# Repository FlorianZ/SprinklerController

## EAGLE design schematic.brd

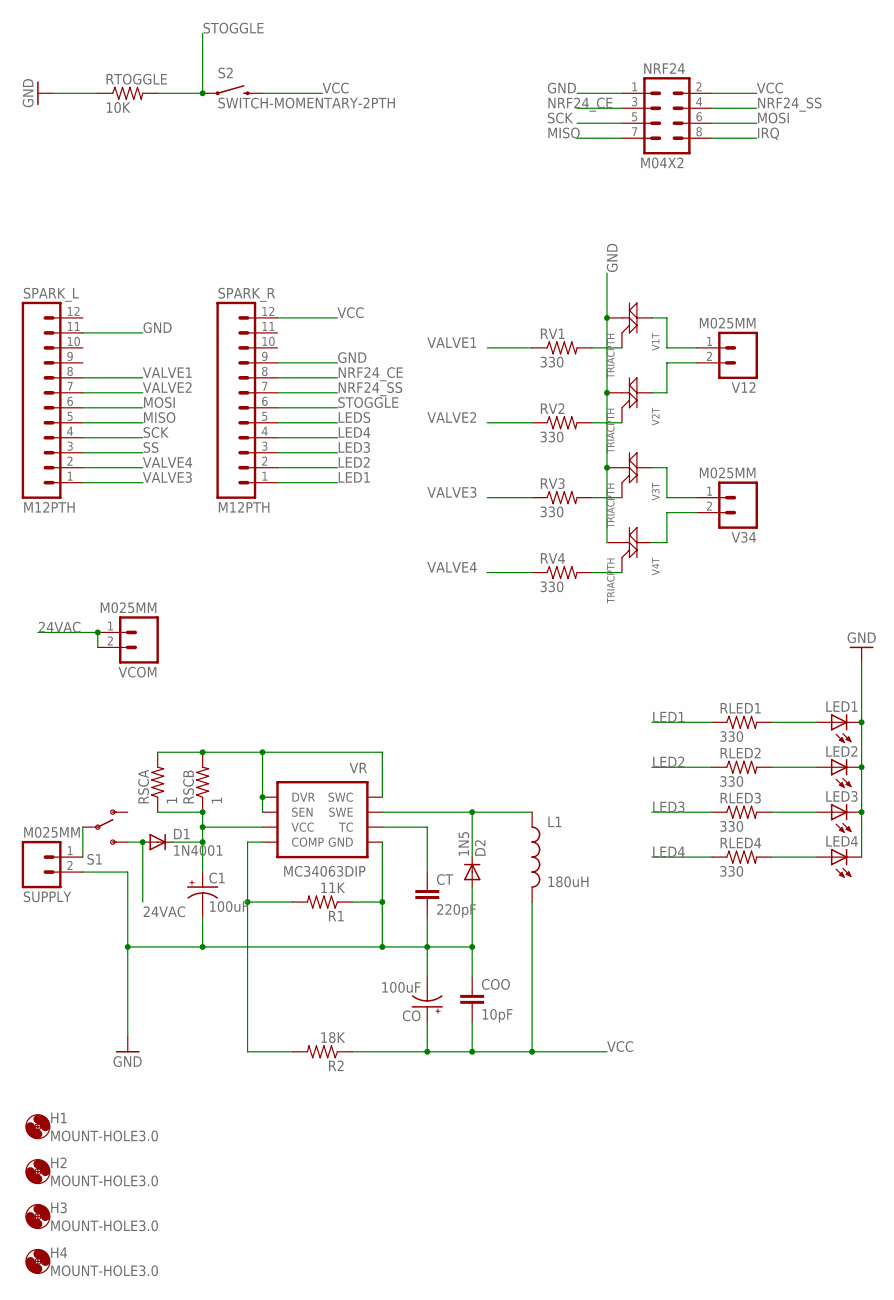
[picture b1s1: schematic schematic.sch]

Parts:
C1: 100uF; E3,5-8
CO: 100uF; CPOL-RADIAL-100UF-25V
COO: 10pF; CAP-PTH-5MM
CT: 220pF; CAP-PTH-5MM
D1: 1N4001; DIODE-1N4001
D2: 1N5; DIODE-1N4001
H1, H2, H3, H4: MOUNT-HOLE3.0; 3,0
L1: 180uH; RLB0912
LED1, LED2, LED3, LED4: LED3MM
NRF24: M04X2; 2X4
R1: 11K; AXIAL-0.3
R2: 18K; AXIAL-0.3
RLED1, RLED2, RLED3, RLED4: 330; AXIAL-0.3
RSCA: 1; AXIAL-0.3
RSCB: 1; AXIAL-0.3
RTOGGLE: 10K; AXIAL-0.3
RV1, RV2, RV3, RV4: 330; AXIAL-0.3
S1: SWITCH-SPDTPTH; SWITCH-SPDT
S2: SWITCH-MOMENTARY-2PTH; TACTILE-PTH
SPARK_L: M12PTH; 1X12
SPARK_R: M12PTH; 1X12
SUPPLY: M025MM; SCREWTERMINAL-5MM-2
V1T, V2T, V3T, V4T: TRIACPTH; TO-92
V12, V34: M025MM; SCREWTERMINAL-5MM-2
VCOM: M025MM; SCREWTERMINAL-5MM-2
VR: MC34063DIP; DIP-08

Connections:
24VAC: D1.A, S1.3 (S), VCOM.1, VCOM.2
GND: C1.-, CO.2 (-), COO.1, CT.2, D2.A, LED1.K (C), LED2.K (C), LED3.K (C), LED4.K (C), NRF24.1, R1.P$1 (1), RTOGGLE.P$1 (1), SPARK_L.11, SPARK_R.9, SUPPLY.2, V1T.1 (M1), V2T.1 (M1), V3T.1 (M1), V4T.1 (M1), VR.4 (GND)
IRQ: NRF24.8
LED1: RLED1.P$1 (1), SPARK_R.1
LED2: RLED2.P$1 (1), SPARK_R.2
LED3: RLED3.P$1 (1), SPARK_R.3
LED4: RLED4.P$1 (1), SPARK_R.4
LEDS: SPARK_R.5
MISO: NRF24.7, SPARK_L.5
MOSI: NRF24.6, SPARK_L.6
unnamed: S1.2, SUPPLY.1
unnamed: V1T.3 (M2), V12.1
unnamed: C1.+, D1.C, RSCA.P$1 (1), RSCB.P$1 (1), VR.6 (VCC)
unnamed: D2.C, L1.1, VR.2 (SWE)
unnamed: RSCA.P$2 (2), RSCB.P$2 (2), VR.1 (SWC), VR.7 (SEN), VR.8 (DVR)
unnamed: CT.1, VR.3 (TC)
unnamed: R1.P$2 (2), R2.P$2 (2), VR.5 (COMP)
unnamed: RV1.P$2 (2), V1T.2 (G)
unnamed: V2T.3 (M2), V12.2
unnamed: RV2.P$2 (2), V2T.2 (G)
unnamed: V3T.3 (M2), V34.1
unnamed: V4T.3 (M2), V34.2
unnamed: RV3.P$2 (2), V3T.2 (G)
unnamed: RV4.P$2 (2), V4T.2 (G)
unnamed: LED1.A, RLED1.P$2 (2)
unnamed: LED2.A, RLED2.P$2 (2)
unnamed: LED3.A, RLED3.P$2 (2)
unnamed: LED4.A, RLED4.P$2 (2)
NRF24_CE: NRF24.3, SPARK_R.8
NRF24_SS: NRF24.4, SPARK_R.7
SCK: NRF24.5, SPARK_L.4
SS: SPARK_L.3
STOGGLE: RTOGGLE.P$2 (2), S2.1, SPARK_R.6
VALVE1: RV1.P$1 (1), SPARK_L.8
VALVE2: RV2.P$1 (1), SPARK_L.7
VALVE3: RV3.P$1 (1), SPARK_L.1
VALVE4: RV4.P$1 (1), SPARK_L.2
VCC: CO.1 (+), COO.2, L1.2, NRF24.2, R2.P$1 (1), S2.3 (2), SPARK_R.12

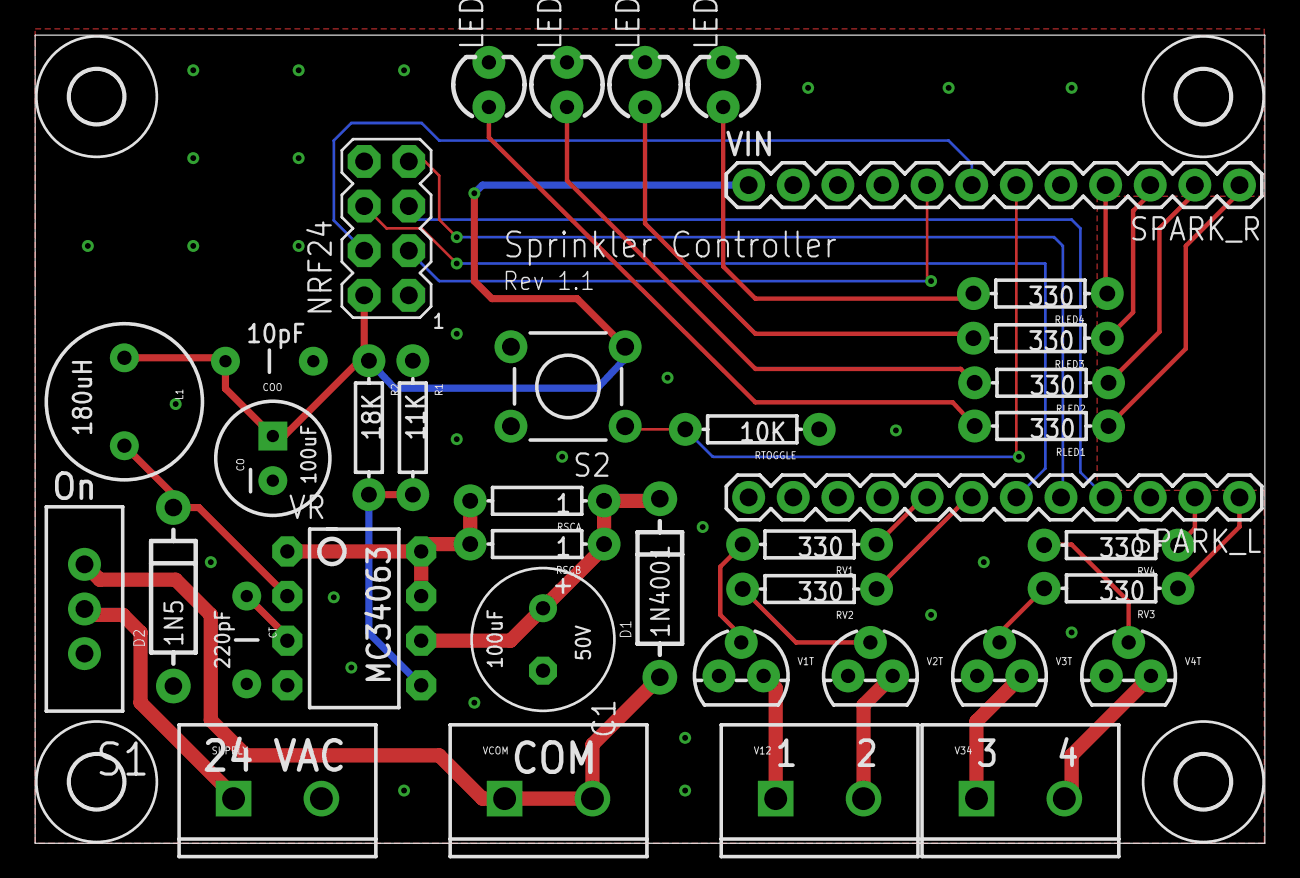
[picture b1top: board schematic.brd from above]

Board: 2 copper layers, 70.0 x 46.0 mm, 42 parts (0 on the bottom side), 35 nets.

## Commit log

2014-04-17 Initial commit.
2014-04-17 Adding .gitignore

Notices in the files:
parts and their libraries:
SparkFun-Electromechanical: Licensing: CC v3.0 Share-Alike You are welcome to use this library for commercial purposes.
